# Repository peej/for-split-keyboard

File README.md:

Split Infinitive is a 6x5x2 key ortholinear split keyboard PCB.

The goal of this project is to build a Let's Split keyboard clone with a number of alternative features:

* Designed to be easy to build with minimal soldering experience.
* Supports both 6x5x2 and 12x5x1 layouts and 2U keys in the bottom corners.
* Switch plate cutouts in the PCB so the same PCB can also be used as a switch plate.
* Serial communication over a TRRS cable in split configuration.
* Single sided PCB, so both halves of the keyboard are identical.

# Bill of Materials (BOM)

* 4 PCBs, 2 for components and 2 as switch plates.
* 60 MX compatible switches.
* 60 1n4148 diodes.
* 1 or 2 Pro Micro controllers with headers or DIP sockets.
* 2 PJ320A 3.5mm TRRS jacks for split configuration.
* TRRS cable and micro USB cable.
* 8 2M standoffs (12mm, depending on required height)
* 16 2M screws
* 60 MX compatible key caps.

## Tools

* Hacksaw blade or similar
* Flat edged file or sanding paper
* Soldering iron and solder

# Ordering PCBs

PCBs can be manufactuered by a variety of online PCB fabricators, the PCB is 114x95mm. You can use [PCBShopper](https://pcbshopper.com/) to search for the best price.

The zip file in the gerber directory contains the gerber files your fabricator will need to make the PCB [for-split.zip](https://github.com/peej/for-split-keyboard/blob/master/gerber/for-split.zip) PCB.

When uploading the gerber zip files, use the default PCB settings. The plate PCB thickness should be 1.6mm for the switches to snap into the plate securely.

# Construction

* You will need 4 PCBs.
* Use the hacksaw blade to remove the 4 support screw holes from the 2 component PCBs.
* Use a hacksaw blade to remove the cutouts for the switch plate PCBs.
* Solder the diodes onto the underside of each PCB.
* Solder on the Pro Micro headers (or a 24 pin DIP socket) onto the underside of each PCB, do not solder on the Pro Micros yet.
  * In split configuration, both PCBs require a Pro Micro so add headers to both PCBs.
  * In non-split configuration, only the master side requires a Pro Micro.
* Solder the PJ320A TRRS sockets onto the underside of each PCB.
  * There are 2 positions per board, use the right position on the left hand PCB and the left position on the right hand PCB.
  * Ensure that the pins will not foul the placement of the switches and still allow the switches to sit flat on the PCB.
  * You may need to slightly bend the pins inwards away from the switch footprint.
* Insert the switches into the plate and then into the top of the PCBs.
  * Insert all the switches and ensure that the pins of each switch are correctly coming through the board and are not bent under the PCB.
  * The top switch that sits underneath the Pro Micro can be inserted in either a north or south facing orientation. North facing helps to prevent it shorting on the Pro Micro components.
* Solder all the switch pins.
* Solder on the Pro Micros, ensure that you get them the correct way around, the chip side should be face down towards the PCB.
* Attach the standoffs to the plate PCB with the screws.
* Connect the halves together with the TRRS cable.
* Flash both Pro Micros with the firmware, see the [QMK documentation](http://qmk.fm/) on how to build and flash the firmware.

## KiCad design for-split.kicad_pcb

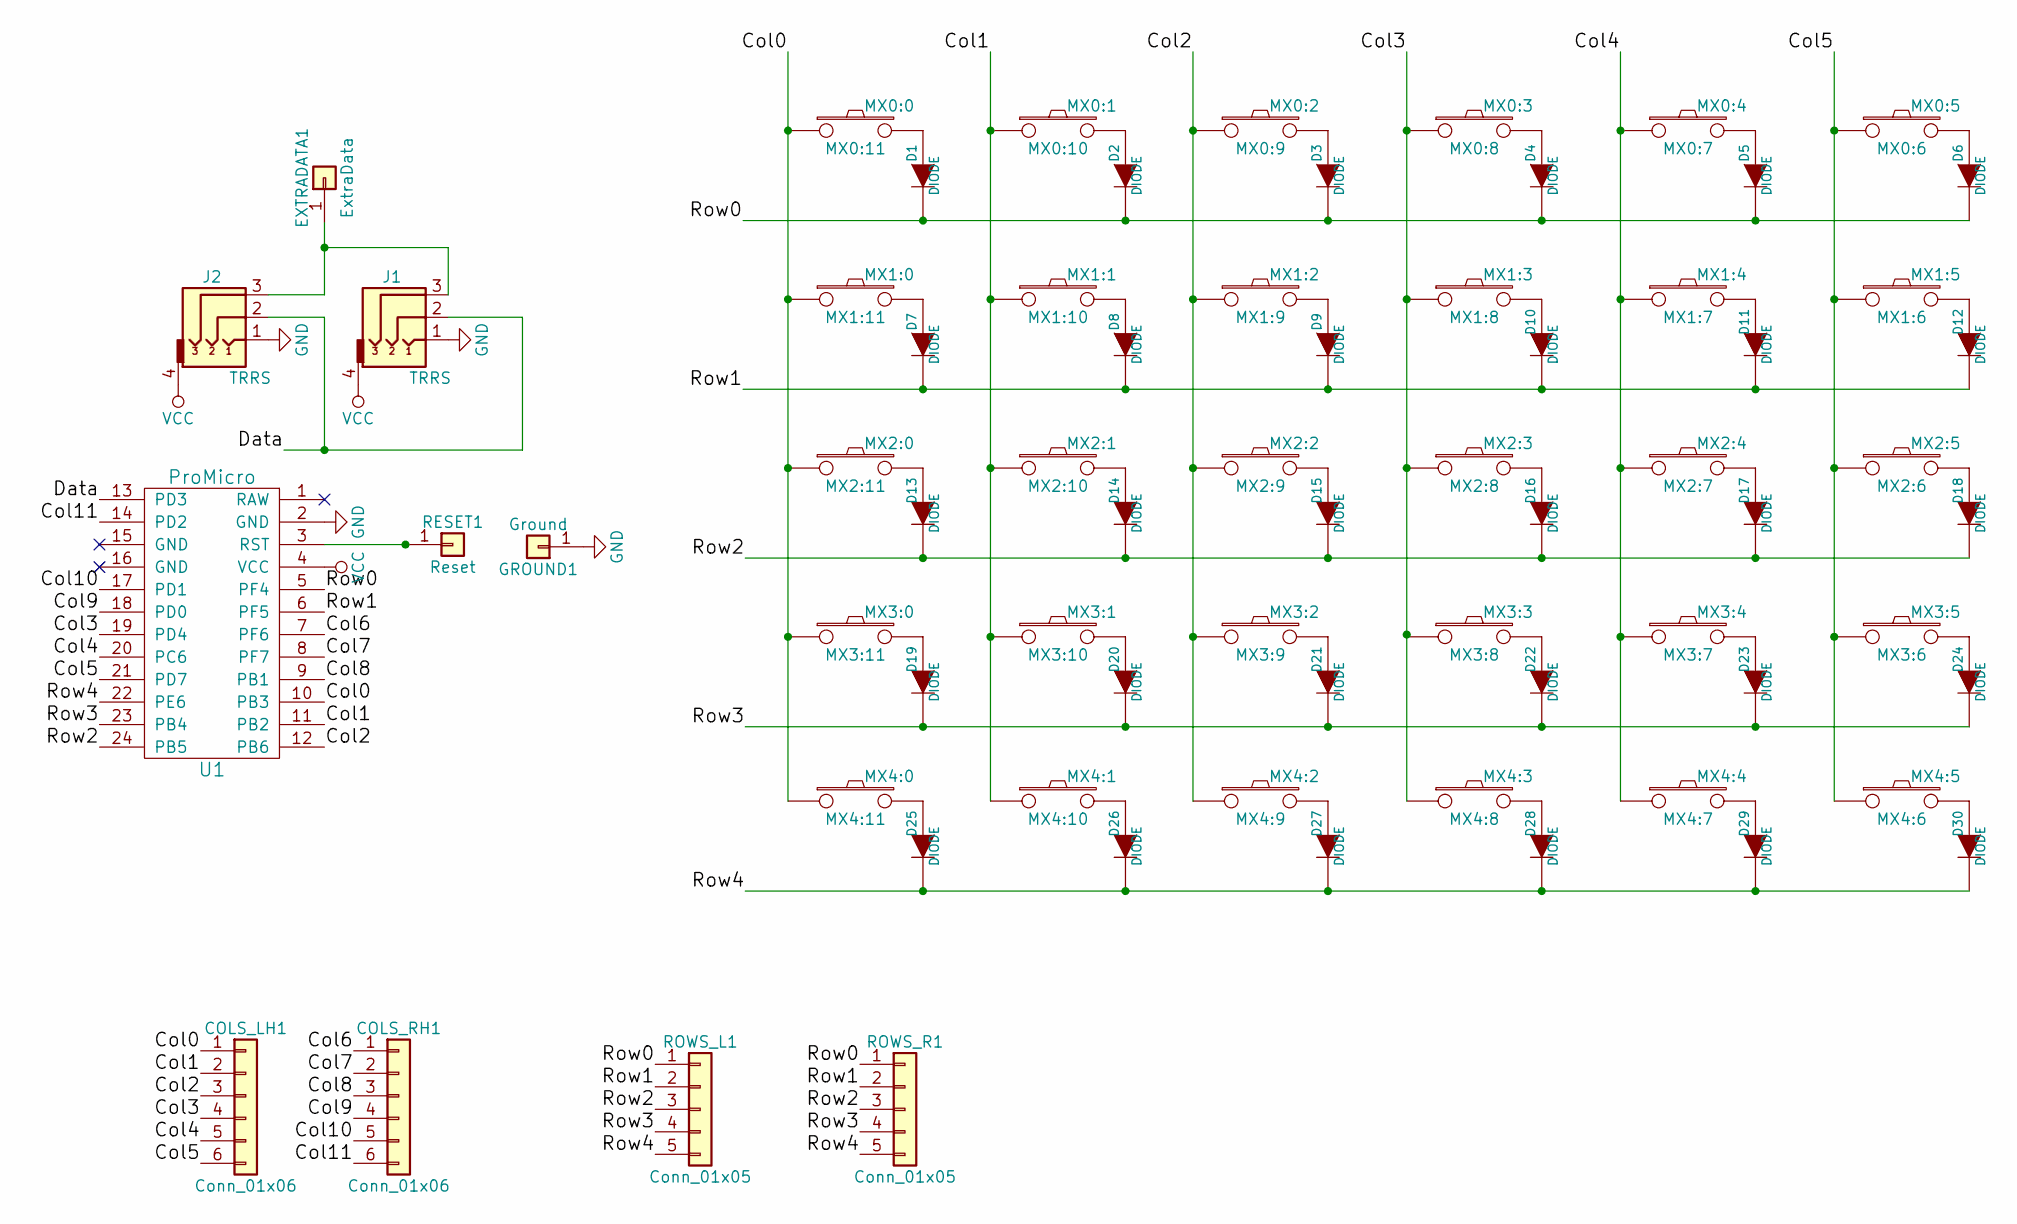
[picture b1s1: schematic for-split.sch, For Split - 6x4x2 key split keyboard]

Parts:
COLS_LH1: Conn_01x06; CONNECTOR_6
COLS_RH1: Conn_01x06; CONNECTOR_6
D1, D2, D3, D4, D5, D6, D7, D8, D9, D10, D11, D12, D13, D14, D15, D16, D17, D18, D19, D20, D21, D22, D23, D24, D25, D26, D27, D28, D29, D30: DIODE
EXTRADATA1: ExtraData; Single_Pad
GROUND1: Ground; Square_Pad
J1, J2: TRRS; PJ-320A
MX0:0: MX0:11; MX_CUTOUT
MX0:1: MX0:10; MX_CUTOUT
MX0:2: MX0:9; MX_CUTOUT_NTHSTH
MX0:3: MX0:8; MX_CUTOUT
MX0:4: MX0:7; MX_CUTOUT
MX0:5: MX0:6; MX_CUTOUT
MX1:0: MX1:11; MX_CUTOUT
MX1:1: MX1:10; MX_CUTOUT
MX1:2: MX1:9; MX_CUTOUT
MX1:3: MX1:8; MX_CUTOUT
MX1:4: MX1:7; MX_CUTOUT
MX1:5: MX1:6; MX_CUTOUT
MX2:0: MX2:11; MX_CUTOUT
MX2:1: MX2:10; MX_CUTOUT
MX2:2: MX2:9; MX_CUTOUT
MX2:3: MX2:8; MX_CUTOUT
MX2:4: MX2:7; MX_CUTOUT
MX2:5: MX2:6; MX_CUTOUT
MX3:0: MX3:11; MX_CUTOUT
MX3:1: MX3:10; MX_CUTOUT
MX3:2: MX3:9; MX_CUTOUT
MX3:3: MX3:8; MX_CUTOUT
MX3:4: MX3:7; MX_CUTOUT
MX3:5: MX3:6; MX_CUTOUT
MX4:0: MX4:11; MX_CUTOUT
MX4:1: MX4:10; MX_CUTOUT
MX4:2: MX4:9; MX_CUTOUT
MX4:3: MX4:8; MX_CUTOUT
MX4:4: MX4:7; MX_CUTOUT
MX4:5: MX4:6; MX_CUTOUT
RESET1: Reset; Square_Pad
ROWS_L1: Conn_01x05; CONNECTOR_5
ROWS_R1: Conn_01x05; CONNECTOR_5
U1: ProMicro; Pro_Micro_ChipSideDown

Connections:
/Col0: COLS_LH1.1, MX0:0.1, MX1:0.1, MX2:0.1, MX3:0.1, MX4:0.1, U1.10 (PB3)
/Col1: COLS_LH1.2, MX0:1.1, MX1:1.1, MX2:1.1, MX3:1.1, MX4:1.1, U1.11 (PB2)
/Col2: COLS_LH1.3, MX0:2.1, MX1:2.1, MX2:2.1, MX3:2.1, MX4:2.1, U1.12 (PB6)
/Col3: COLS_LH1.4, MX0:3.1, MX1:3.1, MX2:3.1, MX3:3.1, MX4:3.1, U1.19 (PD4)
/Col4: COLS_LH1.5, MX0:4.1, MX1:4.1, MX2:4.1, MX3:4.1, MX4:4.1, U1.20 (PC6)
/Col5: COLS_LH1.6, MX0:5.1, MX1:5.1, MX2:5.1, MX3:5.1, MX4:5.1, U1.21 (PD7)
/Col6: COLS_RH1.1, U1.7 (PF6)
/Col7: COLS_RH1.2, U1.8 (PF7)
/Col8: COLS_RH1.3, U1.9 (PB1)
/Col9: COLS_RH1.4, U1.18 (PD0)
/Col10: COLS_RH1.5, U1.17 (PD1)
/Col11: COLS_RH1.6, U1.14 (PD2)
/Data: J1.2, J2.2, U1.13 (PD3)
/Row0: D1.2 (K), D2.2 (K), D3.2 (K), D4.2 (K), D5.2 (K), D6.2 (K), ROWS_L1.1, ROWS_R1.1, U1.5 (PF4)
/Row1: D7.2 (K), D8.2 (K), D9.2 (K), D10.2 (K), D11.2 (K), D12.2 (K), ROWS_L1.2, ROWS_R1.2, U1.6 (PF5)
/Row2: D13.2 (K), D14.2 (K), D15.2 (K), D16.2 (K), D17.2 (K), D18.2 (K), ROWS_L1.3, ROWS_R1.3, U1.24 (PB5)
/Row3: D19.2 (K), D20.2 (K), D21.2 (K), D22.2 (K), D23.2 (K), D24.2 (K), ROWS_L1.4, ROWS_R1.4, U1.23 (PB4)
/Row4: D25.2 (K), D26.2 (K), D27.2 (K), D28.2 (K), D29.2 (K), D30.2 (K), ROWS_L1.5, ROWS_R1.5, U1.22 (PE6)
GND: GROUND1.1, J1.1, J2.1, U1.2 (GND)
unnamed: D1.1 (A), MX0:0.2
unnamed: D2.1 (A), MX0:1.2
unnamed: D3.1 (A), MX0:2.2
unnamed: D4.1 (A), MX0:3.2
unnamed: D5.1 (A), MX0:4.2
unnamed: D6.1 (A), MX0:5.2
unnamed: D7.1 (A), MX1:0.2
unnamed: D8.1 (A), MX1:1.2
unnamed: D9.1 (A), MX1:2.2
unnamed: D10.1 (A), MX1:3.2
unnamed: D11.1 (A), MX1:4.2
unnamed: D12.1 (A), MX1:5.2
unnamed: D13.1 (A), MX2:0.2
unnamed: D14.1 (A), MX2:1.2
unnamed: D15.1 (A), MX2:2.2
unnamed: D16.1 (A), MX2:3.2
unnamed: D17.1 (A), MX2:4.2
unnamed: D18.1 (A), MX2:5.2
unnamed: D19.1 (A), MX3:0.2
unnamed: D20.1 (A), MX3:1.2
unnamed: D21.1 (A), MX3:2.2
unnamed: D22.1 (A), MX3:3.2
unnamed: D23.1 (A), MX3:4.2
unnamed: D24.1 (A), MX3:5.2
unnamed: D25.1 (A), MX4:0.2
unnamed: D26.1 (A), MX4:1.2
unnamed: D27.1 (A), MX4:2.2
unnamed: D28.1 (A), MX4:3.2
unnamed: D29.1 (A), MX4:4.2
unnamed: D30.1 (A), MX4:5.2
unnamed: EXTRADATA1.1, J1.3, J2.3
unnamed: RESET1.1, U1.3 (RST)
VCC: J1.4, J2.4, U1.4 (VCC)

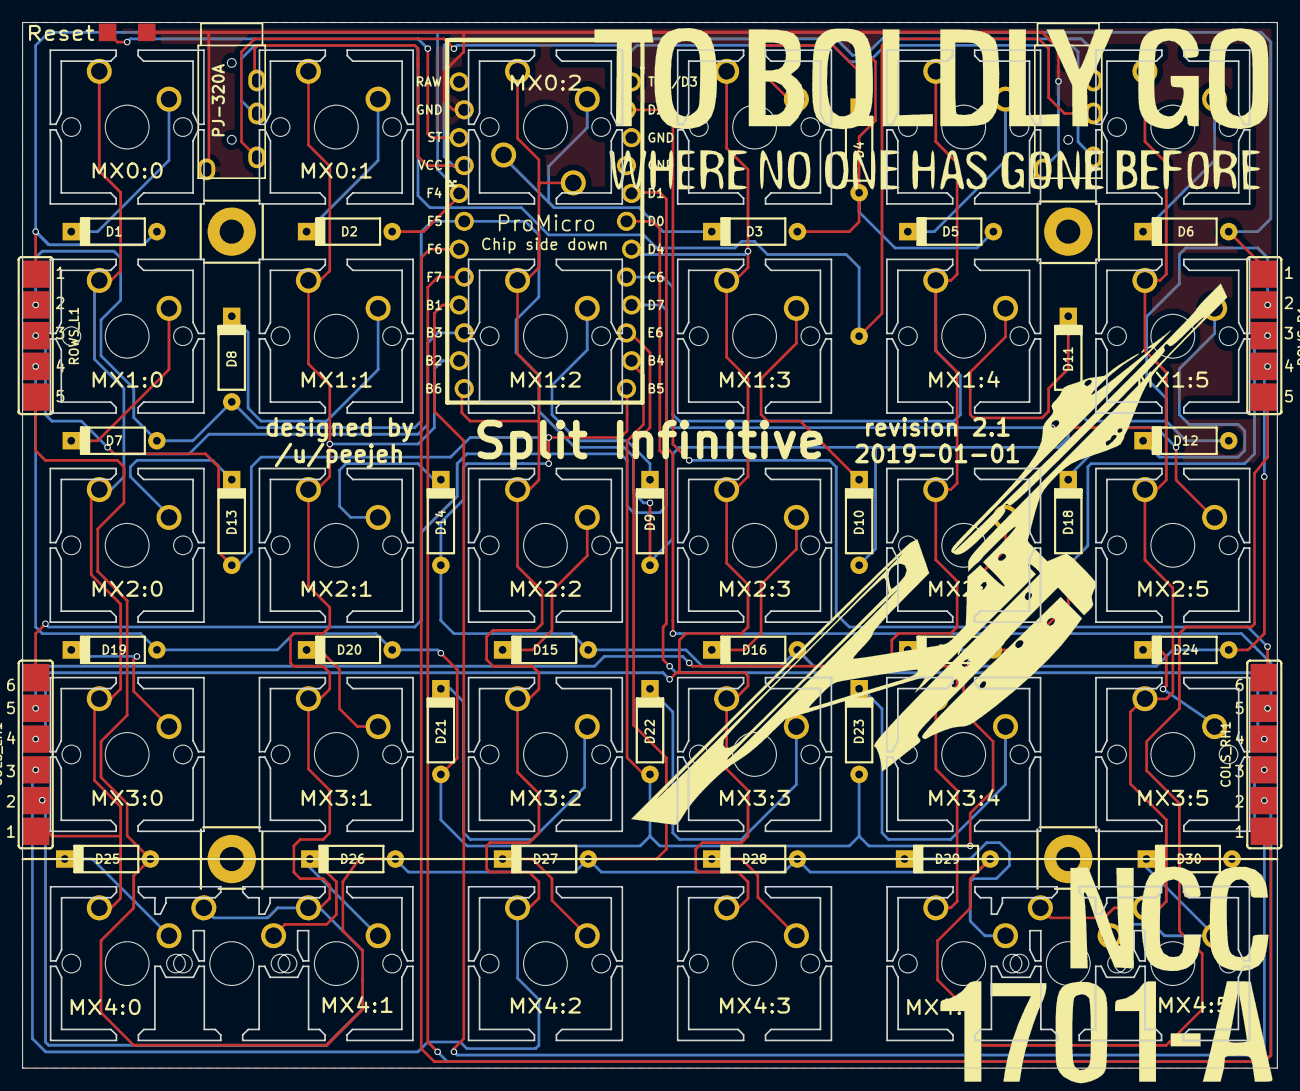
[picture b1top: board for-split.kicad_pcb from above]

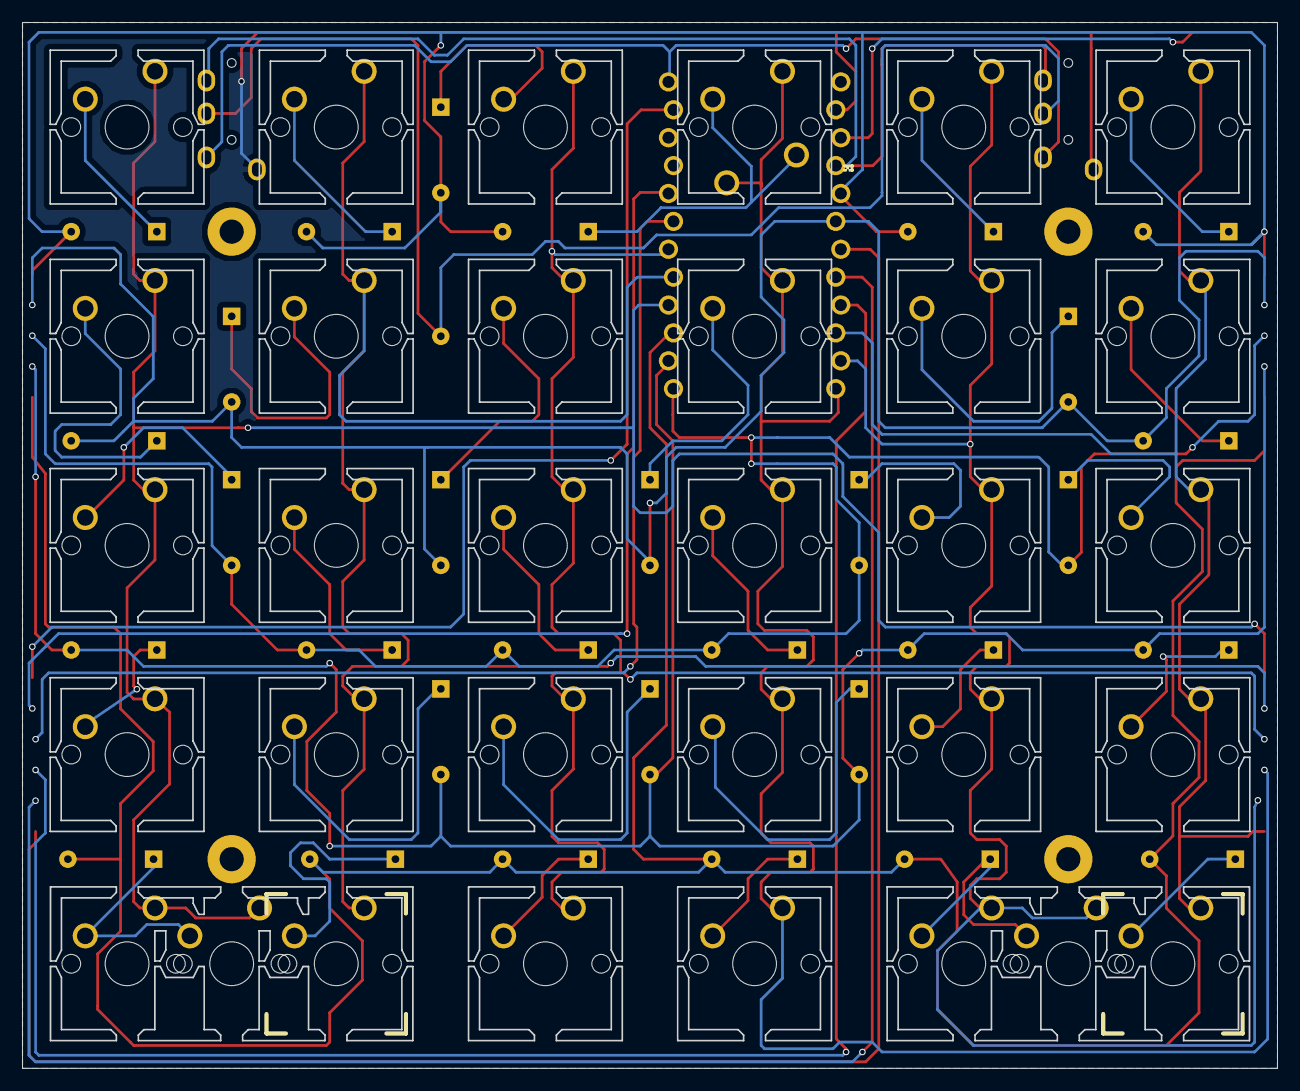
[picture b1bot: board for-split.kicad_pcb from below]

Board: 2 copper layers, 114.3 x 95.2 mm, 74 parts (30 on the bottom side), 52 nets.

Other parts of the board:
Hole: MountingHole; MountingHole_2.2mm_M2_Pad
Hole#2, Hole#3, Hole#4: MountingHole; MountingHole_2.2mm_M2_Pad

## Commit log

2018-02-16 Initial schema and PCB design
2018-02-16 Add gerber files
2018-02-16 Add documentation
2018-02-17 Add extradata pad and connection
2018-02-17 Update gerber files
2018-02-21 Add routes for indicator LEDs
2018-03-18 Increase size of switch cutouts
2018-03-18 Update gerber files for rev2
2018-03-18 Add PCB render to README
2018-03-18 Add custom footprints
2018-03-18 Add cutting markers around standoff holes
2018-03-18 Update instructions in README
2018-03-18 Fix incorrect LED routing
2018-03-25 Add north/south facing option for switch under ProMicro
2018-03-27 Flip LED footprints to correct orientation
2018-03-31 Add custom PJ320D footprint with larger pads
2018-04-01 Switch to through hole PJ320A socket
2018-04-02 Update README with PJ320A instructions
2018-04-07 Fix L2.2 cathode trace
2018-04-14 Remove graphics from backside of PCB
2018-06-15 Add connectors for rows and columns
    Changes have been made to add connectors for the rows and columns so that two PCBs can be bridged together to create a single 12x5 matrix running from a single Pro Micro.
    Provision for removal of the bottom row has been removed to make way for the connectors.
    Holes for 2U stablizers have been removed to increase PCB stiffness.
2018-06-16 Update documentation
2019-01-01 Add zigzag Pro Micro footprint
